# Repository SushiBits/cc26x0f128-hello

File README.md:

# cc26x0f128-hello

> **The avoidance of TI tooling in this project is deliberate.**
>
> Do not raise issues regarding CCS, SysConfig or the TI BLE SDK. Such issues
> will be deleted and their authors blocked immediately. This is not an
> oversight, an unmet prerequisite or a gap to be filled in: the constraint is
> the reason the project exists. Let this serve as forewarning.
>
> This is a moderation rule covering those three tools and nothing wider.
> Issues and pull requests on anything else are welcome.

A bare-metal C starter for the TI CC2640F128 (SimpleLink CC26x0), built on an
open toolchain: GNU make, `arm-none-eabi-gcc`, and a device header generated
from a CMSIS-SVD. No vendor IDE, no vendor SDK, no vendor build system.

**Status: abandoned.** Kept as a record of why, and of the parts that did
work. The short version: the clock setup is vendor code that is at least
readable, but the radio stack is precompiled archives with no source and no
equivalent, so anything using this part as a radio takes TI's tree along with
it. The hardware is being scrapped for a separate reason 鈥?see
[the hardware](#the-hardware-and-why-it-is-being-scrapped). See below.

## Why this is a dead end

**Anything beyond a blink requires the clock setup, the clock setup requires
TI's code, and using this part as a radio requires TI's binary stack. The
constraint was open tools throughout, so there was no version of this that
worked.**

The plan was to treat the CC26x0 like any other Cortex-M3: obtain a CMSIS-SVD,
generate register headers from it, and write the peripheral code directly. The
pipeline for that was built and works. What kills it is what has to be linked
underneath.

### 1. The clock tree needs factory values the manual does not give you

The device starts on its internal high-frequency RC oscillator, and everything
else is derived from it 鈥?`SystemCoreClock` included, which every delay, timer,
baud rate and bus timing scales from. Bringing it up is not a matter of setting
a divider: the oscillator has to be calibrated against values measured on each
individual die at final test.

Those values live in FCFG1, and the ones that matter are all marked "Internal.
Only to be used through TI provided API":

| FCFG1 register | Purpose |
|---|---|
| `SHDW_OSC_BIAS_LDO_TRIM` | oscillator bias and LDO trim |
| `SHDW_ANA_TRIM` | analog block trim |
| `ANA2_TRIM` | analog block trim |
| `LDO_TRIM` | LDO trim |
| `RCOSC_HF_TEMPCOMP` | HF RC oscillator temperature compensation |
| `CONFIG_OSC_TOP` | top-level oscillator configuration |
| `AMPCOMP_TH1`, `AMPCOMP_TH2`, `AMPCOMP_CTRL1` | amplitude compensation thresholds |
| `CAP_TRIM` | oscillator cap-array trim |
| `VOLT_TRIM` | voltage trim |

54 of FCFG1's 83 registers carry that marker. Only `MISC_TRIM` and `OSC_CONF`
are documented at all.

So the manual tells you a register exists and withholds what belongs in it.
There is no published source for those values and no description of how to
interpret them. Reading them out blind and writing them back is guesswork with
an oscillator.

### 2. The clock setup is vendor code 鈥?and the ROM is a distraction

TI's answer to the above is driverlib, and driverlib is genuinely open:
BSD-3-Clause, readable, patchable, redistributable. It also contains the clock
setup in full. `setup.c` is a complete 394-line `SetupTrimDevice` that reads
FCFG1 and trims the device, and all ten `ROM_*` calls in `osc.c` have a
`NOROM_` source equivalent 鈥?`OSCClockSourceSet`, `OSCHF_TurnOnXosc`,
`OSCHF_AttemptToSwitchToXosc` and the rest.

That last point matters, because it removes the mask ROM from the argument.
`ROM_SetupTrimDevice` and the `ROM_OSC*` family are flash-saving duplicates of
behaviour that is published as readable source in the same package. Redirecting
a call site to the `NOROM_` implementation is a `#define`; the ROM is never
required. So a card that ships a ROM block is not a disclosure problem when the
same logic is available as source 鈥?and here it is.

What is genuinely undocumented is narrower: the FCFG1 calibration the code
consumes. You can read exactly what `SetupTrimDevice` does with each value, but
not what the values mean, because their field semantics are what the manual
declines to document. So the clock is inspectable, and reimplementable only
with the source in hand 鈥?but not verifiable against a specification, and not
writable from published information alone.

That is a real limit, and it is a modest one. It is not the limit that kills
this project. The next finding is.

### 3. The radio is a binary, and unlike the ROM it has no source equivalent

The RF core is a separate Cortex-M0 running TI-supplied firmware, and the BLE
protocol stack ships as precompiled archives with no source: hundreds of them
in `blelib/`, `cc2640_ctrl_*.a` at 0.7鈥?.1 MB each and `host_*.a` at 1.0鈥?.8 MB
each, plus the HCI transport layers. Nothing in the SDK corresponds to them.

This is where the ROM comparison stops being a distraction and becomes the
argument. For the oscillator, TI publishes the logic as source and the ROM is
optional. For the radio, there is no source at all, no `NOROM_` equivalent, and
no way to build a link without the archives. There is no register-level path to
a working radio either, so the binary is not a convenience 鈥?it is the only
implementation that exists.

Which means using this part as a radio means adopting TI's build system,
TI-RTOS and XDCtools along with the archives. A project that chooses that
deliberately is a normal project. This one did not, and could not: the
constraint was open tools, and the radio alone violates it regardless of
anything else in the tree.

Worth being explicit about what would fix it, since it is not exotic. TI could
document the ROM in the reference manual or an application note, and an
operator could then show that document to an inspector 鈥?the oscillator case is
already nearly there, because driverlib's source is the reference. No
equivalent exists for the stack, and no amount of documentation substitutes for
source when the question is what the transmitter is actually doing.

### 4. The device description that might have bypassed all of it does not exist

**No vendor SVD exists.** Neither BLE SDK 2.2 nor the cc26xxware package it
depends on contains one, and a recursive search of the whole `C:\ti` install
(BLE SDK 2.2, TI-RTOS, SysConfig, MSPM0 SDK) returns zero `.svd` files. What
TI ships instead is hand-maintained `hw_*.h` register headers 鈥?an equivalent
for humans, not an input for a generator.

**SysConfig is not an alternative.** Its device data is JSON under
`dist\deviceData\<PART>\<PART>.json`, but searching a 414 kB device file for
`register`, `bitfield`, `interrupt`, `addressOffset` and `baseAddress` returns
zero hits for all five. It carries pinmux, packages, power domains and cores.
There is no register data to convert, and there is no `CC2640F128` part entry
either 鈥?only the CC2640R2F variants. No converter, however written, can
recover information that is not there.

**The one published SVD is defective.** `cmsis-svd-data` carries
`data/TexasInstruments/CC26x0.svd` v2.3, which is TI-derived and covers the
right registers. It is not directly consumable:

- Interrupt `<value>` entries are byte offsets into the vector table, not IRQ
  numbers. Fed to a generator unmodified, it produced
  `I2C_IRQ_IRQn = 4` and `TRNG_IRQ_IRQn = 132`, which displaces every NVIC
  call and the entire handler table by a factor of four, with no error.
- 48 violations of the CMSIS-SVD 1.0 schema (`alternateRegister` used as a
  child of `register`, empty `<fields>`, empty `<description>`, hex strings in
  an `xs:integer` field).
- **All 3242 field descriptions are the field name repeated.** There is no
  semantic content at all 鈥?`CALC_EN` is documented as "CALC_EN".

That last point is what matters most for the SVD route. Even after the other
defects are corrected, the SVD is an address map without meaning: it says a
bit exists at position 7, not what it does.

### 5. What the manual does document, it does not share

`swcu117i.pdf` contains 1441 occurrences of "Only to be used through TI
provided API" 鈥?the semantic content an SVD cannot supply and the manual
declines to. Separately, the manual is copyrighted, so even the documented
half cannot be redistributed next to the code that depends on it.

## The same method, on two parts

This was not a question of difficulty, and it is worth recording why, because
the same technique was applied to TI's MSPM0 family first and worked: take the
vendor's per-peripheral headers, rebuild them into a CMSIS-SVD, generate a
device header, drive the registers directly. That is a reasonable amount of
work and it pays off.

The same approach here does not pay off, and the difference is measurable in
the same units on both families:

| | MSPM0 | CC26x0 |
|---|---|---|
| CMSIS-SVD shipped by TI | none | none |
| per-peripheral header tree | 43 files, 6.5 MB | 58 files |
| "Only to be used through TI provided API" in those headers | **0** | **1054**, across 15 files |
| the same phrase in the reference manual | **0** in 6.0 M characters | **1441** in 3.0 M characters |
| header-to-SVD rebuild | viable 鈥?the manual specifies the registers | not viable 鈥?the clock cannot be specified from published material |

The MSPM0 manual (SLAU847, 6.0 M characters extracted) does not contain the
phrase at all. The CC26x0 manual (SWCU117, 3.0 M characters) contains it once
every ~2,100 characters.

In the headers it is concentrated precisely where it does the most damage:

| Header | Occurrences |
|---|---|
| `hw_flash.h` | 322 |
| `hw_fcfg1.h` | 231 |
| `hw_adi_0_rf.h` | 159 |
| `hw_adi_3_refsys.h` | 66 |
| `hw_ddi_0_osc.h` | 61 |
| `hw_adi_4_aux.h` | 57 |

`hw_fcfg1.h` is the factory calibration from finding 1, and `hw_ddi_0_osc.h`
is the oscillator controller. The two headers that would have to be understood
to bring up a clock are the second and fifth most withheld in the tree.

So the conclusion is not that this was too hard, or that the tooling was
missing. A method that works on one TI family is defeated on another by what
the documentation chooses to say, in a way no amount of engineering effort
recovers.

## Why it could never have been maintained

Openness is a licensing argument. This is the practical one, and it is the one
that decides whether the result is a project or a one-off.

The test is whether `git clone && make` works. That is what makes a project
maintainable at all: a new contributor builds it, CI builds it, a bisect
builds it, and a bug report from two years ago can be reproduced.

With the radio in the tree, that test cannot pass, and the licence is why:

- **The blobs cannot be redistributed.** The SDK licence permits distribution
  only as "embedded executable copies of such Licensed Materials that execute
  solely and exclusively on, or in conjunction with, TI Devices" (搂iv). They
  cannot be committed, vendored, mirrored, or attached to a release.
- **The download cannot be delegated.** 搂11 requires the downloader to make
  export-control representations personally 鈥?that they are not located in or
  under the control of an embargoed country, are not on the SDN or Denied
  Persons lists, and will not use the materials for weapons end-uses. A CI
  runner cannot make those representations on a contributor's behalf, and a
  hosted service has no business accepting them. There is also a PRC
  registration obligation in 搂11a that falls on the recipient.
- **The binary cannot be inspected to work around it.** The licence forbids
  reverse engineering the object-code portions, "nor permit any person or
  entity to do so" 鈥?which closes the obvious fallback of disassembling the
  stack to demonstrate what it does.

So every consumer must obtain the SDK individually, accept terms in their own
name, and end up with a dependency that cannot be pinned by content hash,
cannot be cached, cannot be mirrored, and cannot be audited. Builds are not
hermetic; two people with the same commit do not have the same inputs.

The result is a class of project that is buildable exactly once, by the person
who assembled it, on the machine where they assembled it. Not a library, not a
platform, not something anyone can fork and fix. One-off. Consumable. That is
what "e-waste" means in engineering terms rather than as an insult: an artefact
whose value cannot outlive its assembly.

**This repository is the proof by construction.** It builds from a fresh clone
鈥?public submodules, `make`, zero errors, 1480 bytes of text 鈥?precisely
because it dropped the radio. Reproducibility was not achieved alongside the
dead end; it was achieved *by* accepting the dead end.

## Where the black box sits

The question is not whether a black box exists. Silicon is opaque, always, and
that is not a problem. The question is where the boundary falls — because that
is what decides whether anyone can point at it.

Auditors and compliance reviewers accept a boundary they can treat as a fact: a
die, a core, a discrete flashed artefact with an address and a version. What
nobody can work with is an opaque region with no edge, because there is then
nothing to name, hash, version, replace or declare.

Three ways to ship a radio, in order of how well they survive scrutiny:

**AT86RF233 — the boundary is the die.** A transceiver with no firmware at all:
a documented register interface over SPI, and every line that drives it is
yours. Your firmware contains no vendor code, so auditing means checking your
own source against the datasheet. The split is silicon, which means it is a fact
about the part and survives any build system. This is the normal shape of a
hardware component, and it is fine.

**MM32W073PFB — the same boundary, on one package.** An MM32F073 Cortex-M0 with
a 2.4GHz transceiver beside it in a single package, and it stays in this
category rather than dropping to a worse one. The radio is hardware with a
register interface — an AT86RF231-style design, by its owner's reading — not
firmware on a second core, so whether the two blocks share a die or only a
package changes nothing an auditor cares about. Integration is not what makes a
boundary unverifiable. A CPU executing vendor code is.

It is also discontinued, which is the other half of the same problem. An
auditable part you can no longer buy is still a supply risk; it is simply a
different one from an unauditable part you can.

**STM32WB55 — the boundary is a core.** The wireless firmware is a binary too,
but it runs on the M0+ and is flashed as its own image. ST is explicit about the
split: "All the code running on CPU2 is delivered as an encrypted binary.
Blackbox for customer perspective" (AN5289 §4.1), and "the customer has only
access to CPU1 core and sees the firmware running on CPU2 as a blackbox"
(§10.4). Two things follow. The opaque part has an address, a version and a hash,
so it can be declared and attested even if it cannot be read — and the system
clock on CPU1 is yours to write from a reference manual that documents the
bits. Bounded, attributable, and reproducible by anyone with the binary, which
SLA0044 permits redistributing.

**CC26x0 — the boundary is a vendor toolchain, and only there.** The stack
arrives as `.a` archives. TI's own IAR flow does produce a separate stack image:
`lib_search.exe` generates the link list from `blelib/`, and `frontier.exe`
applies a `.bdef`/`.xcl` boundary in a post-build step. But that split is a
property of their build tools, not of the silicon. Hand-roll the build — which
is the entire premise of this repository — and there is no `frontier` step: the
archives link into your image and the boundary reverts to what it structurally
is, which is none.

It is also worse than a linking question, and this is where the leeching shows.
A radio does not run on its own clock. Everything derives from the system clock,
which is set up by vendor code executing on *your* core, reading factory
calibration values whose semantics the manual withholds. So even if the radio
were sealed off tomorrow, vendor logic would still be inside your firmware,
because the clock tree the radio depends on is vendor-written and cannot be
rewritten from published information. There is no line that excludes it.

Nor does it help that this code only writes numbers into registers. A
calibration constant applied to an oscillator register whose derivation is
undocumented is not merely as opaque as an encrypted blob — it is worse, in two
ways a blob is not.

A blob can be attested. Flash the vendor's image, hash it, compare that against
the copy they published: identical hashes are evidence of provenance that an
auditor can accept without reading a single byte. Calibration constants admit no
such check. They are measured on each die at final test and differ from device
to device, so there is no upstream value to compare against, no hash that means
anything, and nothing to declare in an SBOM beyond "read out of the chip at
runtime".

And they are not incidental. The trim sets the oscillator's frequency accuracy,
which is precisely what certification measures and what an inspection asks
about: the carrier offset decides whether a transmitter stays inside its
allocation. `ccfg.c` shows the shape of it, where
`MODE_CONF_XOSC_CAPARRAY_DELTA` is a signed 8-bit per-device adjustment applied
directly to the trimmed crystal cap-array value. In a diff, in a review, in an
SBOM, that number is indistinguishable from one you chose yourself. The blob at
least announces that it is a blob; the constant says nothing at all.

There is a configuration structure — CCFG, the last 88 bytes of flash — and it
does not help. It is not a register interface that hardware consults; it is a
parameter block that code at a fixed address reads. Every access to it in the
SDK is software: `setup.c` and `osc.c` read it while trimming, `setup_rom.c`
mirrors what the boot ROM does with it, and `flash.c` takes its sector-protection
offsets from it.

That mechanism is not itself a defect, and it would be wrong to present it as
one. Renesas RA parts do the same thing: option-setting memory sits at fixed
addresses in flash, consumed by the boot ROM and by reset-time hardware options,
and FSP fills it from ordinary compile-time constants — `BSP_CFG_OPTION_SETTING_OFS0`
and `OFS1` placed into `.option_setting_ofs0` and `.option_setting_ofs1`. A
flash-resident config block read by immutable ROM is an ordinary design, and on a
part whose fields are documented it is a perfectly workable one. A bare-metal
RA2E1 port that keeps its option bytes in an ordinary `config.c`, with no FSP in
the build at all and device headers generated from a vendor-supplied SVD, is at
[SushiBits/ra2e1-hello](https://github.com/SushiBits/ra2e1-hello).

What differs is what the fields mean. Renesas documents its option bytes, so the
constants that produce them can be chosen, reviewed and defended. CCFG's fields
do not stand on their own. Three of them are defined only as offsets against
values the manual does not document: `MODE_CONF_1.DELTA_IBIAS_INIT` and
`DELTA_IBIAS_OFFSET` are each specified as "See FCFG1:AMPCOMP_CTRL1.IBIAS_INIT"
and "…IBIAS_OFFSET", and `MODE_CONF.VDDR_TRIM_SLEEP_DELTA` as "See
FCFG1:VOLT_TRIM.VDDR_TRIM_SLEEP_H". To set them you need the semantics of the
internal registers, which is precisely what cannot be obtained.

Had those registers been documented, none of this would be necessary. The same
intent would be a handful of `#define`s in a project header — compile-time
constants the compiler folds into a short chain of writes, or read-modify-writes,
against registers whose meaning you can state and defend. That is not a
hypothetical shape: it is what Renesas ships. The structure is not the problem.
The withheld semantics are.

There is a second axis, and it decides whether an opaque part may be *explained*
rather than merely declared. TI's licence forbids reverse engineering the object
code — "nor permit any person or entity to do so" — so the one route that could
convert a blob into an answer is closed by contract, not merely blocked by
effort.

Not every vendor does that. Espressif ships its Wi-Fi and Bluetooth stacks as
binary archives under Apache-2.0, published in a public repository in Object
form, which carries no such restriction. The boundary is still inside the image
and the source is still absent, but a determined reader may lawfully disassemble
it and write down what it does. ST's wireless firmware sits between the two: the
licence is permissive, but the image is delivered encrypted, so permission to
look is not the same as an ability to.

For the purpose this document cares about — accounting for a transmitter to
somebody — the right to investigate matters more than the presence of source.
Source is the easy case. The hard case is a blob, and it is not one case: a blob
you may lawfully disassemble, a blob you are permitted to look at but cannot, and
a blob you are contractually forbidden to touch are three different positions
with three different answers.

That is the shape of the difference, and it is not about size or licence text.
AT86RF233 puts the box in silicon and STM32WB55 puts it on another core; both
boundaries are facts about the part that survive being rebuilt by anybody. The
CC26x0 puts it inside your image, behind a split that only the vendor's tooling
can produce, with the clock tree — the thing everything else depends on —
vendor-supplied and unspecified. The first is fully auditable. The second is
auditable at its boundary. Only the third leaves you unable to answer the
question at all.

Which is the irony worth recording, because TI's customers for these dev kits
are overwhelmingly companies, and companies are the ones who have to produce
auditable evidence: security review, supply-chain attestation, certification
against functional-safety or medical standards, and — increasingly — software
bill-of-materials obligations. Those obligations attach to the shipped image. A
component that cannot be declared in an SBOM, cannot be reviewed, and cannot be
replaced is a procurement problem before it is an ideological one. The closed
shape here is least suited to exactly the customer it is aimed at.

## Auditability is a delivery requirement, not a preference

That obligation is no longer a matter of taste, and it lands on the integrator,
who these regimes treat as the manufacturer:

- **EU Cyber Resilience Act** (Reg. (EU) 2024/2847) 鈥?in force since December
  2024 with obligations phasing in through 2027: vulnerability handling,
  security updates for a defined support period, and a software bill of
  materials.
- **FDA 搂524B** of the FD&C Act 鈥?premarket cybersecurity for medical devices,
  including an SBOM and a monitoring and patching plan.
- **IEC 62443** for industrial automation and **UN R155** for automotive 鈥?
  component-level transparency pushed down the supply chain.

An SBOM can *name* a binary. It cannot characterise one, and none of these
regimes is satisfied by the vendor's assurance that a blob is fine.

And the radio stack is not an incidental blob. It is remotely reachable. The
precedent is **SweynTooth** (2020): 18 vulnerabilities across the BLE SDKs of
six SoC vendors, producing deadlocks, crashes, buffer overflows and in one case
a bypass of the pairing procedure. **TI was among the affected vendors, with
three CVEs in that set targeting the CC26xx family** 鈥?CVE-2019-17520,
CVE-2019-19193 and CVE-2020-13593.

So the question a compliance function asks is not academic: *when the next one
lands, can you tell whether you are affected, and can you remediate?* Here the
answer is no twice over. The controller cannot be rebuilt, so a fix exists only
at TI's discretion and only if they choose to ship one for this part; and where
logic sits in silicon rather than flash, not even then.

Unpatchable is not an inconvenience. It is a liability with a name attached.
That is why an unauditable radio stack fails security review before it ever
reaches a licensing review 鈥?and why this is a project killer rather than an
aesthetic objection.

## The hardware, and why it is being scrapped

The KiCad sources in `hardware/` are kept for the record. **Do not fabricate
this board.**

The design drives the antenna through an RF front-end module rather than from
the CC2640 directly: an AT2401C PA/LNA behind a 2450BM14G0011 balun and filter,
with the matching network following TI's SWRA117D. That was deliberate 鈥?it was
meant to extend range.

It also takes the board out of the unlicensed regime. With the FEM in the path
the output no longer fits inside the conducted and EIRP limits for an
unlicensed intentional radiator under FCC Part 15, and the same applies to the
equivalents in ETSI and SRRC. A board like this cannot be certified, and cannot
lawfully be operated as a Part 15 device. What it is instead is amateur radio
equipment.

That in itself would be fine. Home-built transmitters are a normal part of the
hobby, and they do not need certification. But amateur operation carries its
own obligations, and one of them is that the station must be open to
inspection: the operator has to be able to account for what the equipment is
and what it emits.

A firmware image that links a radio stack supplied as unreadable archives
cannot be accounted for 鈥?not by the operator to an inspector, and not by
anyone downstream. The clock is not the obstacle here: driverlib's source is
readable, and a mask ROM with a published source equivalent is a flash
optimisation, not a secrecy problem. The stack is the obstacle, because there
is nothing to read, no equivalent to substitute, and the licence forbids
disassembling it to demonstrate what it does.

So the two failures compound. The FEM turned the board into a transmitter that
needs amateur rules in order to be legal at all. The closed radio stack made it
a transmitter that cannot satisfy those rules. Neither is fixable within this
design, which is why the boards are being scrapped rather than shelved.

*This is the reasoning behind the decision, not legal advice; the specifics
vary by jurisdiction.*

## The rest of the record

The sections below are what the attempt produced. They are accurate and are
the reason this repository is published rather than deleted, but none of them
supply a clock setup or a radio stack.

## What is documented, and why it does not matter

A detail worth recording, because it shows the conclusion is not simply "the
documentation is unusable".

In the SVD, the "Internal" marker appears on **207 of 969 registers, 21.4%**,
and it is heavily concentrated:

| Peripheral | Registers marked internal |
|---|---|
| FLASH | 122 / 123 |
| FCFG1 | 54 / 83 |
| AUX_SCE | 10 / 10 |
| AON_BATMON | 9 / 13 |
| AUX_ADI4 | 5 / 11 |
| AON_IOC | 3 / 5 |
| CPU_TIPROP | 2 / 2 |
| PRCM | 1 / 56 |

**34 of 43 peripherals are entirely clean**: GPIO (15/15), IOC (32/32), PRCM
(56/57), UART0 (14/14), SSI0/1 (10/10), I2C0 (18/18), GPT0-3 (29/29 each),
UDMA0 (19/19), WDT (9/9), CRYPTO (40/40), TRNG (22/22). The manual agrees:
clustering its 1441 occurrences by nearby peripheral name gives VIMS 476,
PRCM 66, FCFG1 7, IOC 2, and **zero** within 卤400 characters of GPIO, UART,
SSI, I2C, GPT, WDT, UDMA, CRYPTO or TRNG.

So on paper the peripherals are well documented. It does not help, and the
distinction is worth being exact about: a documented register is not a working
peripheral. GPIO, UART, SPI, I2C and the timers all take their timing from the
clock tree, and the clock tree needs driverlib. The registers being described
does not make them reachable without something to set the clock up.

## What works

The pipeline is complete and was verified against TI's own headers rather than
against the SVD's claims:

```
contrib/platform/share/CC26x0F128.svd
  -> contrib/svdconv          -> contrib/platform/include/CC26x0F128.h
  -> contrib/irqn             -> contrib/platform/include/CC26x0F128_handlers.h
  -> CC26x0F128_it.c          -> vector table
```

- The SVD was normalized (interrupt values divided by four, schema violations
  removed, device renamed so the header filename is right) and now validates
  with zero schema errors. `svdconv` reports zero errors and zero warnings.
- **42/42** peripheral base addresses match `hw_memmap.h`.
- **33/33** external interrupts and **10/10** core exceptions match `hw_ints.h`.
- IRQ 3 remains a skip, matching the gap in TI's own `startup_gcc.c` table.
- The memory map was corrected to 128 kB flash (130,984 usable bytes), 20 kB
  SRAM and 8 kB GPRAM, following the four linker files TI ships.
- `systick.c`, the startup code and the system layer compile against the
  generated header, and `make` links.

That is where it stops. The code builds and links, but the tick it configures
is derived from the clock tree that driverlib would have to set up, so it would
not run as built.

## What is unfinished

Left in place rather than papered over:

- **The LED is not driven.** `main.c` starts the tick and loops. The DIO the
  LED sits on has to come from the schematic and be muxed through IOC before
  GPIO sees it; that was not done.
- **Nothing populates CCFG.** The linker script reserves the last 88 bytes of
  flash as the `CCFG` region, but no `.ccfg` section is emitted, so the chip
  reads whatever the flash happens to contain there. TI's `ccfg.c` is the
  reference for doing it properly.
- `.vscode/launch.json` still points its `svdFile` at `MSPM0L130X.svd`.
- `src/systick.c` explains its interrupt masking in terms of Cortex-M0 lacking
  exclusive access instructions. The masking is still correct on this part;
  the reasoning no longer applies to an M3.
- `.vscode/c_cpp_properties.json` defines `HSE_VALUE=24000000`, an STM32-ism.
- The vendored submodules are pinned but `contrib/cmsis` tracks a release tag
  while `contrib/irqn` and `contrib/svdconv` track branch heads.

## If someone wants to continue

The SVD work in this repository is reusable as-is: the normalized device
description, the verification against TI's headers, and the generation
pipeline are all correct and independent of the application.

Continuing means accepting two dependencies: TI's clock code, and 鈥?for
anything using the radio 鈥?TI's precompiled stack. The first is a reasonable
trade; driverlib is BSD-3-Clause, readable and patchable, and reimplementing it
against undocumented calibration data is worse in every way. The second is the
one that matters, because there is no alternative to it at all.

`cc26xxware` (driverlib plus the `hw_*.h` headers) on top of the BLE SDK's
build system is the supported arrangement and it works. What it is not is a
free-standing open stack: the clock has no specification and the radio has no
source. A project content to depend on TI for those two things is perfectly
viable 鈥?it just is not the project this repository was.

## Layout

| Path | Contents |
|---|---|
| `src/` | application: `main.c`, `systick.c` |
| `include/` | application headers |
| `lib/` | board linker script |
| `contrib/platform/` | device layer: memory map, startup, system, SVD |
| `contrib/cmsis` | submodule: ARM CMSIS 6 |
| `contrib/irqn` | submodule: handler-table generator |
| `contrib/svdconv` | submodule: SVD to header generator |
| `hardware/` | KiCad sources for the CC2640 EVM 鈥?do not fabricate, see above |
| `docs/` | not tracked; see below |

## Building

Requires `arm-none-eabi-gcc`, `make` and `python3`. Submodules must be checked
out. Device headers are generated, never committed:

```
git submodule update --init --recursive
make          # generates headers, then builds
make size     # flash and SRAM usage
make distclean
```

`docs/*.pdf` is ignored: TI's datasheet, technical reference manual
(SWCU117I), antenna note (SWRA117D) and the EVM schematic are copyrighted and
are not redistributed here. To get them back:

| Document | Source |
|---|---|
| `cc2640.pdf` (datasheet) | <https://www.ti.com/lit/ds/symlink/cc2640.pdf> |
| `swcu117i.pdf` (technical reference manual) | <https://www.ti.com/lit/ug/swcu117i/swcu117i.pdf> |
| `swra117d.pdf` (antenna measurements) | <https://www.ti.com/lit/an/swra117d/swra117d.pdf> |
| `cc2640-evm.pdf` | re-plot from `hardware/cc2640-evm.kicad_sch` (KiCad, Plot to PDF) |

## Licence

BSD 3-Clause; see [LICENSE.md](LICENSE.md). The licence grants copyright
rights only. Trademark terms are in [TRADEMARKS.md](TRADEMARKS.md).

`contrib/platform/share/CC26x0F128.svd` is derived from the device description
published by the [cmsis-svd-data](https://github.com/cmsis-svd/cmsis-svd-data)
project, itself derived from TI's device database. It is included here because
it cannot be obtained in this corrected form anywhere else; review TI's terms
before redistributing it further.

No TI SDK, BLE stack or other TI object code is included, because none of it
may be redistributed. This repository contains no vendor binaries at all, which
is why it is self-contained and why it cannot use the radio.

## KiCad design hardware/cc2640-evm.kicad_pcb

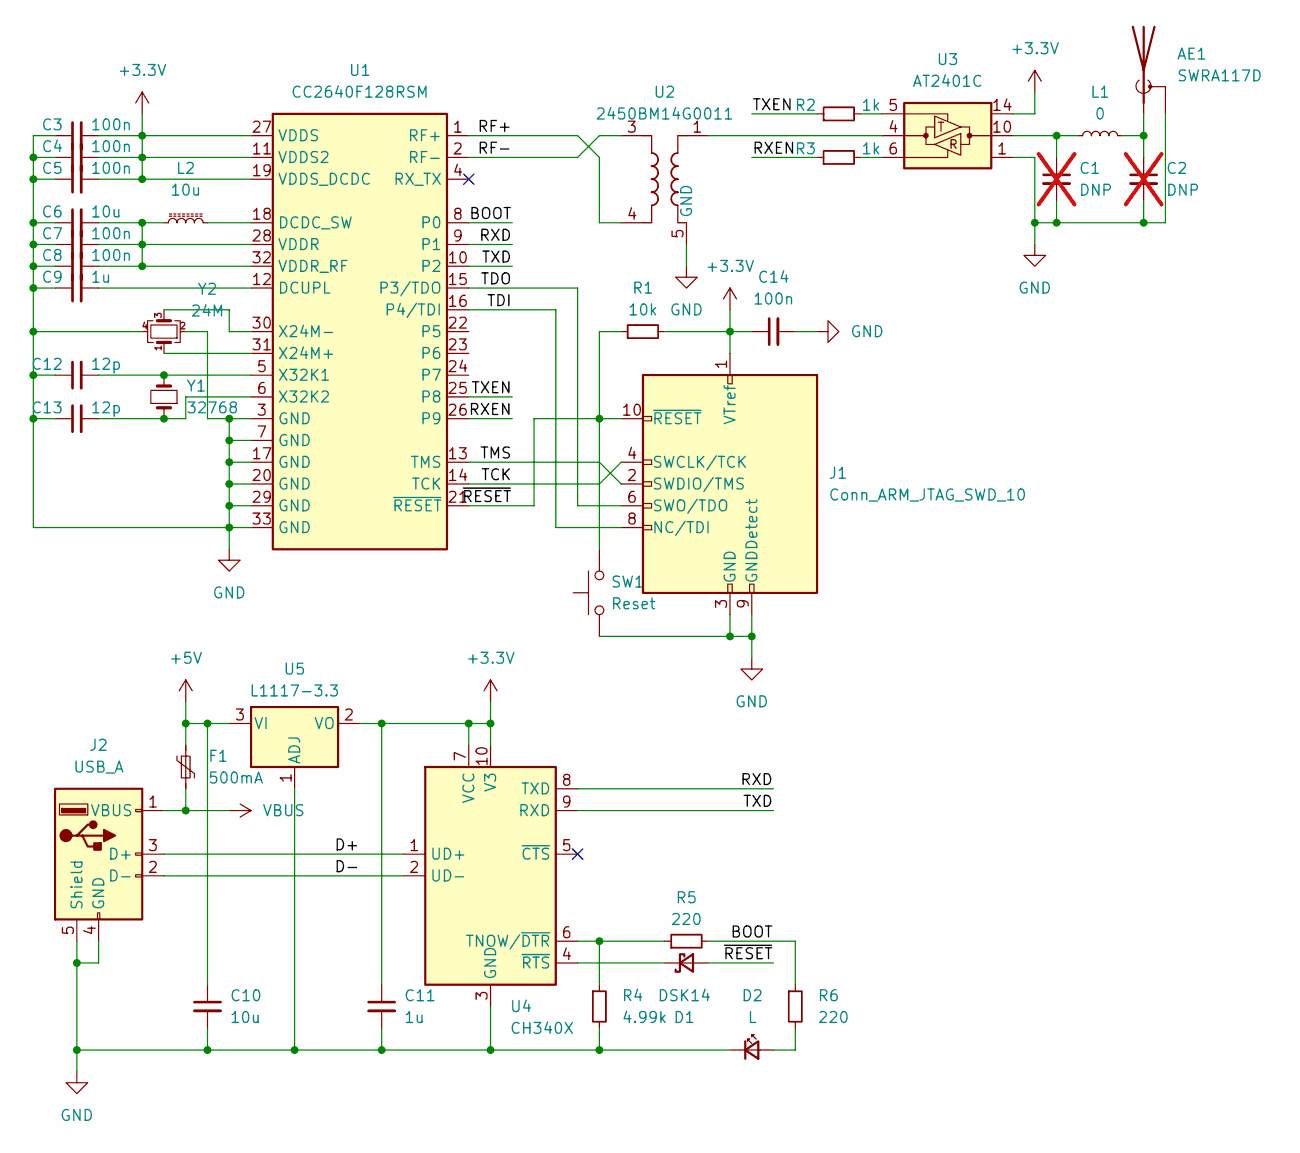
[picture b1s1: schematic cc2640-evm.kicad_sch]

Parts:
AE1: SWRA117D; Texas_SWRA117D_2.4GHz_Left
C1, C2: DNP; C_0603_1608Metric_Pad1.08x0.95mm_HandSolder; not fitted
C3, C4, C5, C7, C8, C14: 100n; C_0603_1608Metric_Pad1.08x0.95mm_HandSolder
C6, C10: 10u; C_0603_1608Metric_Pad1.08x0.95mm_HandSolder
C9, C11: 1u; C_0603_1608Metric_Pad1.08x0.95mm_HandSolder
C12, C13: 12p; C_0603_1608Metric_Pad1.08x0.95mm_HandSolder
D1: DSK14; D_SOD-323
D2: L; LED_0805_2012Metric_Pad1.15x1.40mm_HandSolder
F1: 500mA; Fuse_0805_2012Metric_Pad1.15x1.40mm_HandSolder
J1: Conn_ARM_JTAG_SWD_10; PinHeader_2x05_P1.27mm_Vertical
J2: USB_A; USB_A_CNCTech_1001-011-01101_Horizontal
L1: 0; L_0603_1608Metric_Pad1.05x0.95mm_HandSolder
L2: 10u; L_0805_2012Metric_Pad1.15x1.40mm_HandSolder
R1: 10k; R_0603_1608Metric_Pad0.98x0.95mm_HandSolder
R2, R3: 1k; R_0603_1608Metric_Pad0.98x0.95mm_HandSolder
R4: 4.99k; R_0603_1608Metric_Pad0.98x0.95mm_HandSolder
R5, R6: 220; R_0603_1608Metric_Pad0.98x0.95mm_HandSolder
SW1: Reset; SW_Push_SPST_NO_Alps_SKRK
U1: CC2640F128RSM; QFN-32-1EP_4x4mm_P0.4mm_EP2.9x2.9mm
U2: 2450BM14G0011; Balun_Johanson_1.6x0.8mm
U3: AT2401C; WQFN-16-1EP_3x3mm_P0.5mm_EP1.68x1.68mm
U4: CH340X; MSOP-10_3x3mm_P0.5mm
U5: L1117-3.3; SOT-89-3
Y1: 32768; Crystal_SMD_3215-2Pin_3.2x1.5mm
Y2: 24M; Crystal_SMD_3225-4Pin_3.2x2.5mm

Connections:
+3.3V: C3.2, C4.2, C5.2, C11.1, C14.1, J1.1 (VTref), R1.2, U1.11 (VDDS2), U1.19 (VDDS_DCDC), U1.27 (VDDS), U3.14 (VDD), U3.16 (VCC), U4.7 (VCC), U4.10 (V3), U5.2 (VO)
+5V: C10.1, F1.1, U5.3 (VI)
/BOOT: R5.2, R6.1, U1.8 (P0)
/D+: J2.3 (D+), U4.1 (UD+)
/D-: J2.2 (D-), U4.2 (UD-)
/RF+: U1.1 (RF+), U2.4
/RF-: U1.2 (RF-), U2.3
/RXD: U1.9 (P1), U4.8 (TXD)
/RXEN: R3.1, U1.26 (P9)
/TCK: J1.4 (SWCLK/TCK), U1.14 (TCK)
/TDI: J1.8 (NC/TDI), U1.16 (P4/TDI)
/TDO: J1.6 (SWO/TDO), U1.15 (P3/TDO)
/TMS: J1.2 (SWDIO/TMS), U1.13 (TMS)
/TXD: U1.10 (P2), U4.9 (RXD)
/TXEN: R2.1, U1.25 (P8)
/~RESET: D1.2 (A), J1.10 (~RESET), R1.1, SW1.2, U1.21 (~RESET)
GND: AE1.2 (Shield), C1.2, C2.2, C3.1, C4.1, C5.1, C6.1, C7.1, C8.1, C9.1, C10.2, C11.2, C12.1, C13.1, C14.2, D2.1 (K), J1.3 (GND), J1.5 (GND), J1.9 (GNDDetect), J2.4 (GND), J2.5 (Shield), R4.2, SW1.1, U1.3 (GND), U1.7 (GND), U1.17 (GND), U1.20 (GND), U1.29 (GND), U1.33 (GND), U2.5 (GND), U2.6 (GND), U3.1 (GND), U3.2 (GND), U3.3 (GND), U3.7 (GND), U3.8 (GND), U3.9 (GND), U3.11 (GND), U3.12 (GND), U3.15 (GND), U3.17 (GND), U4.3 (GND), U5.1 (ADJ), Y2.2, Y2.4
unnamed: AE1.1 (A), AE1.r (A), C2.1, L1.2
unnamed: D1.1 (K), U4.4 (~RTS)
unnamed: D2.2 (A), R6.2
unnamed: L2.2, U1.18 (DCDC_SW)
unnamed: C9.2, U1.12 (DCUPL)
unnamed: C6.2, C7.2, C8.2, L2.1, U1.28 (VDDR), U1.32 (VDDR_RF)
unnamed: U1.31 (X24M+), Y2.1
unnamed: U1.30 (X24M-), Y2.3
unnamed: C12.2, U1.5 (X32K1), Y1.2
unnamed: C13.2, U1.6 (X32K2), Y1.1
unnamed: C1.1, L1.1, U3.10 (ANT)
unnamed: R3.2, U3.6 (RXEN)
unnamed: R2.2, U3.5 (TXEN)
unnamed: U2.1, U3.4 (TXRX)
unnamed: R4.1, R5.1, U4.6 (TNOW/~DTR)
VBUS: F1.2, J2.1 (VBUS)

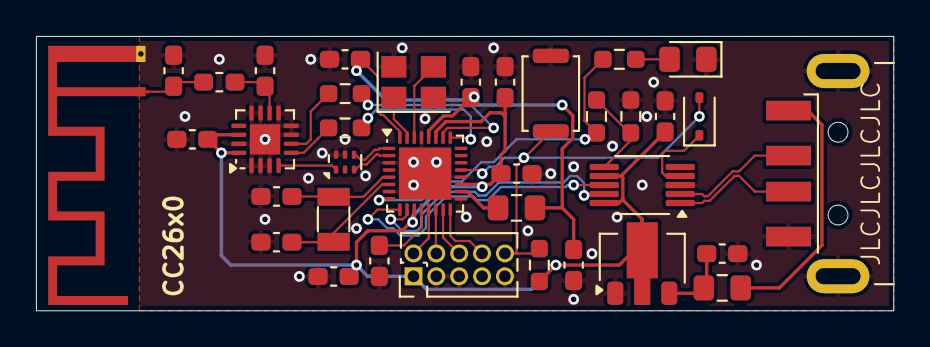
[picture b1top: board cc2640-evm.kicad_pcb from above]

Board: 2 copper layers, 47.6 x 15.2 mm, 36 parts (0 on the bottom side), 33 nets.
